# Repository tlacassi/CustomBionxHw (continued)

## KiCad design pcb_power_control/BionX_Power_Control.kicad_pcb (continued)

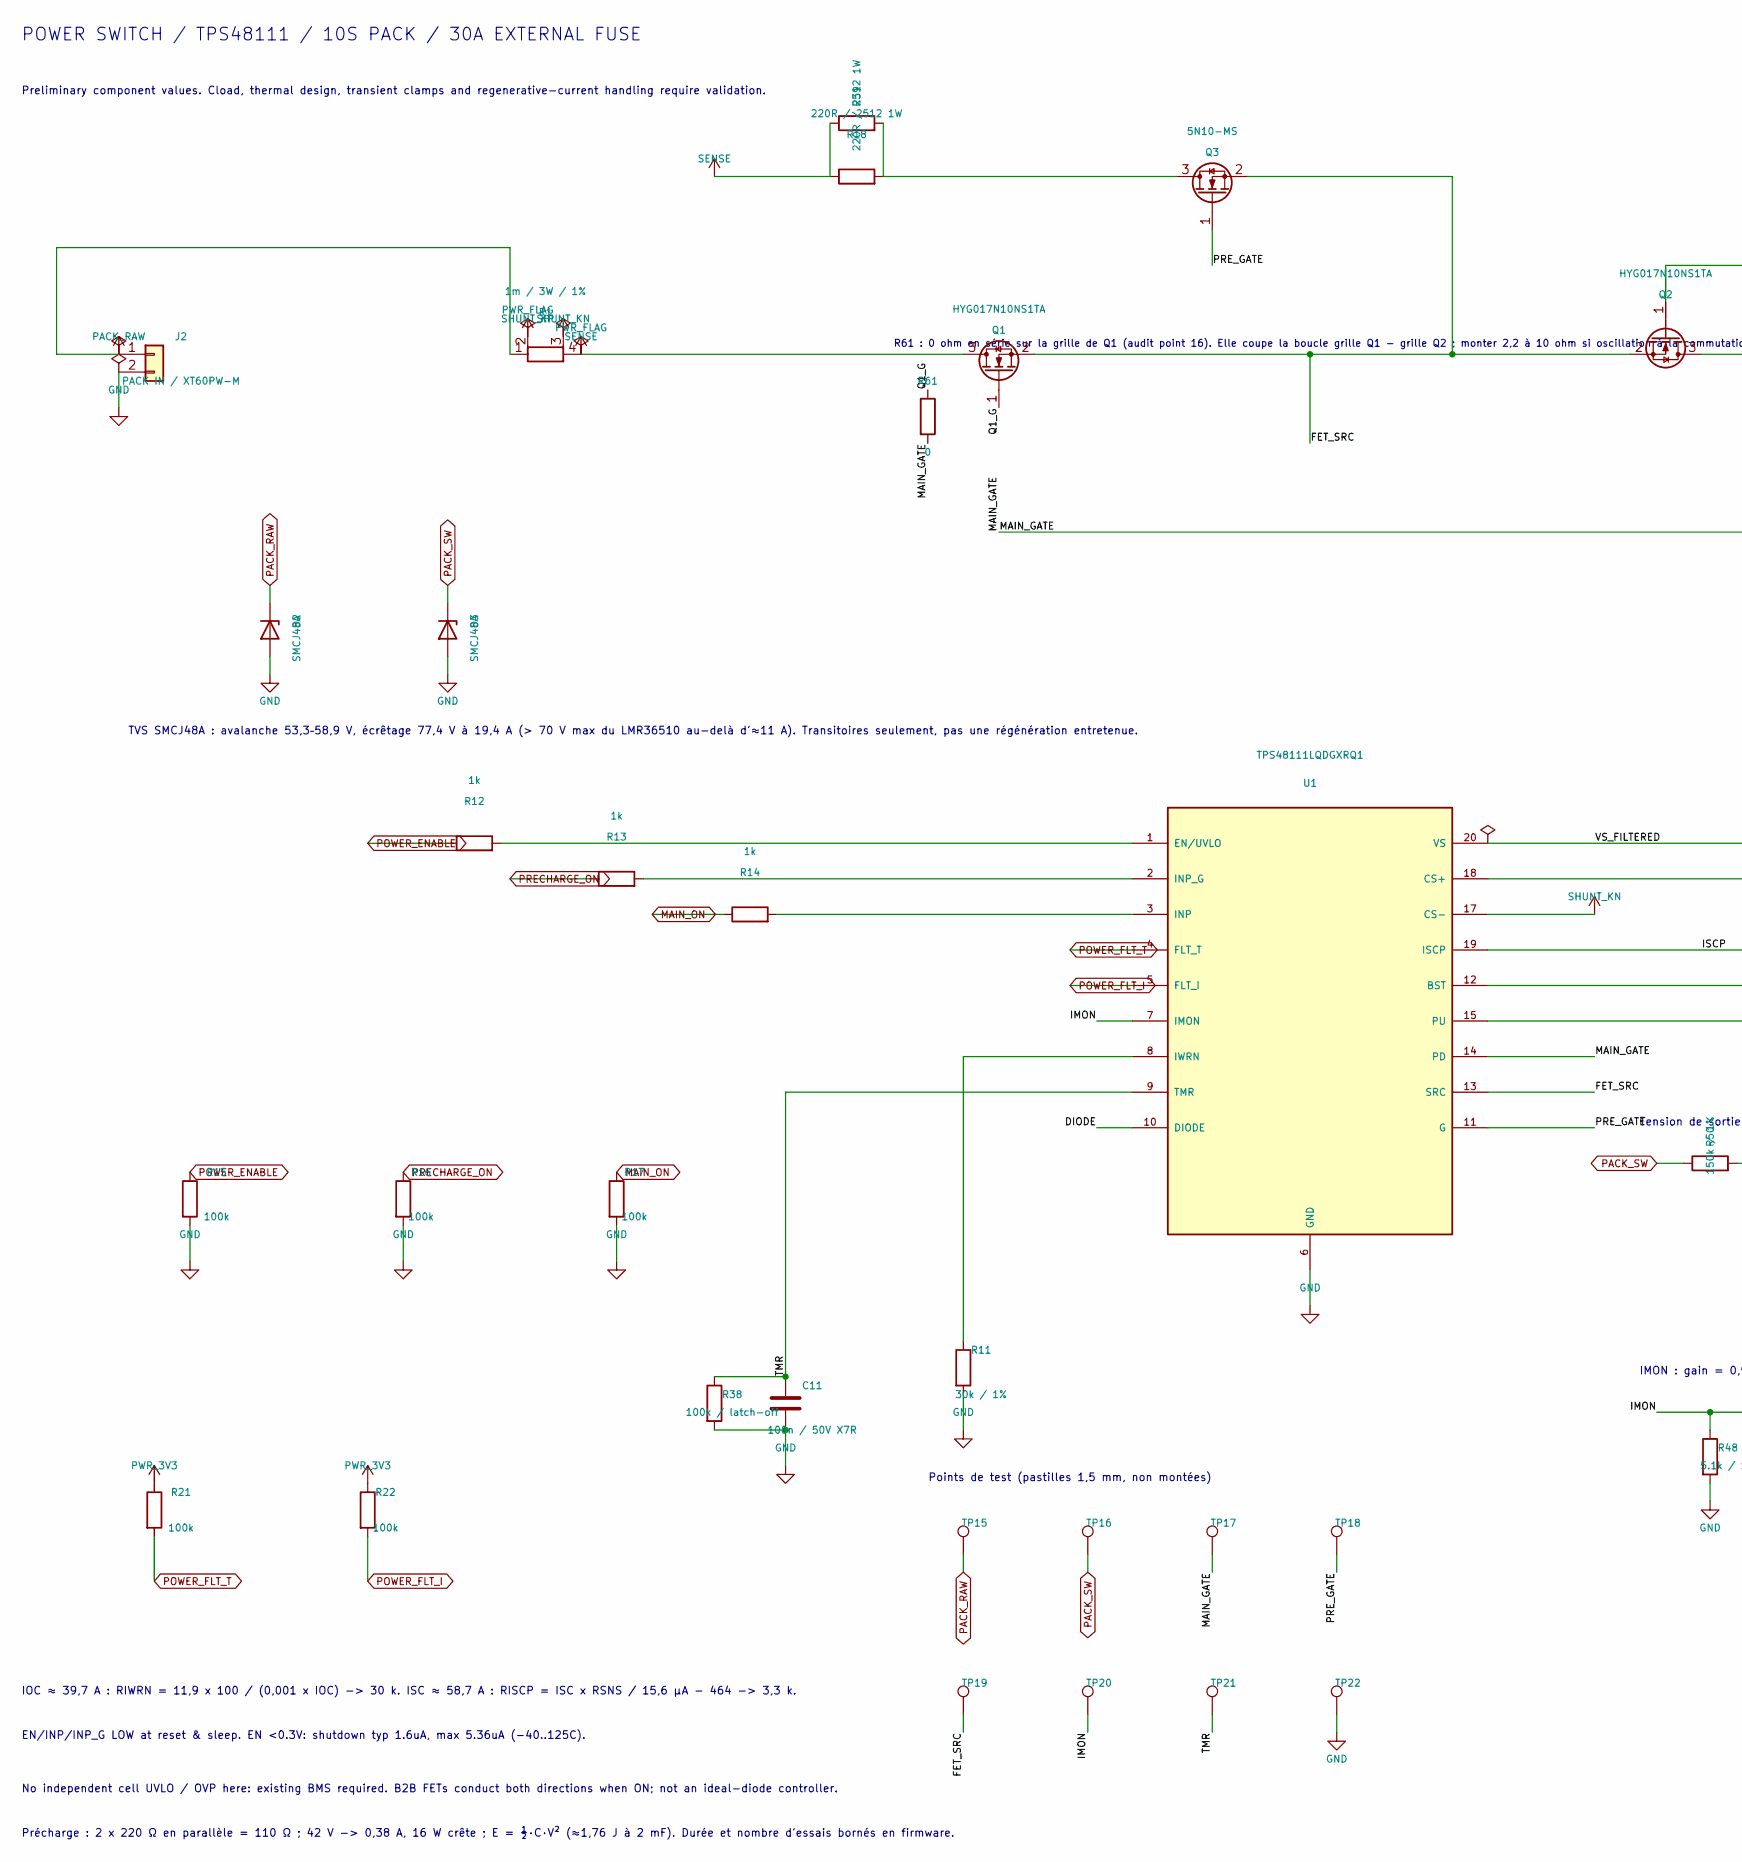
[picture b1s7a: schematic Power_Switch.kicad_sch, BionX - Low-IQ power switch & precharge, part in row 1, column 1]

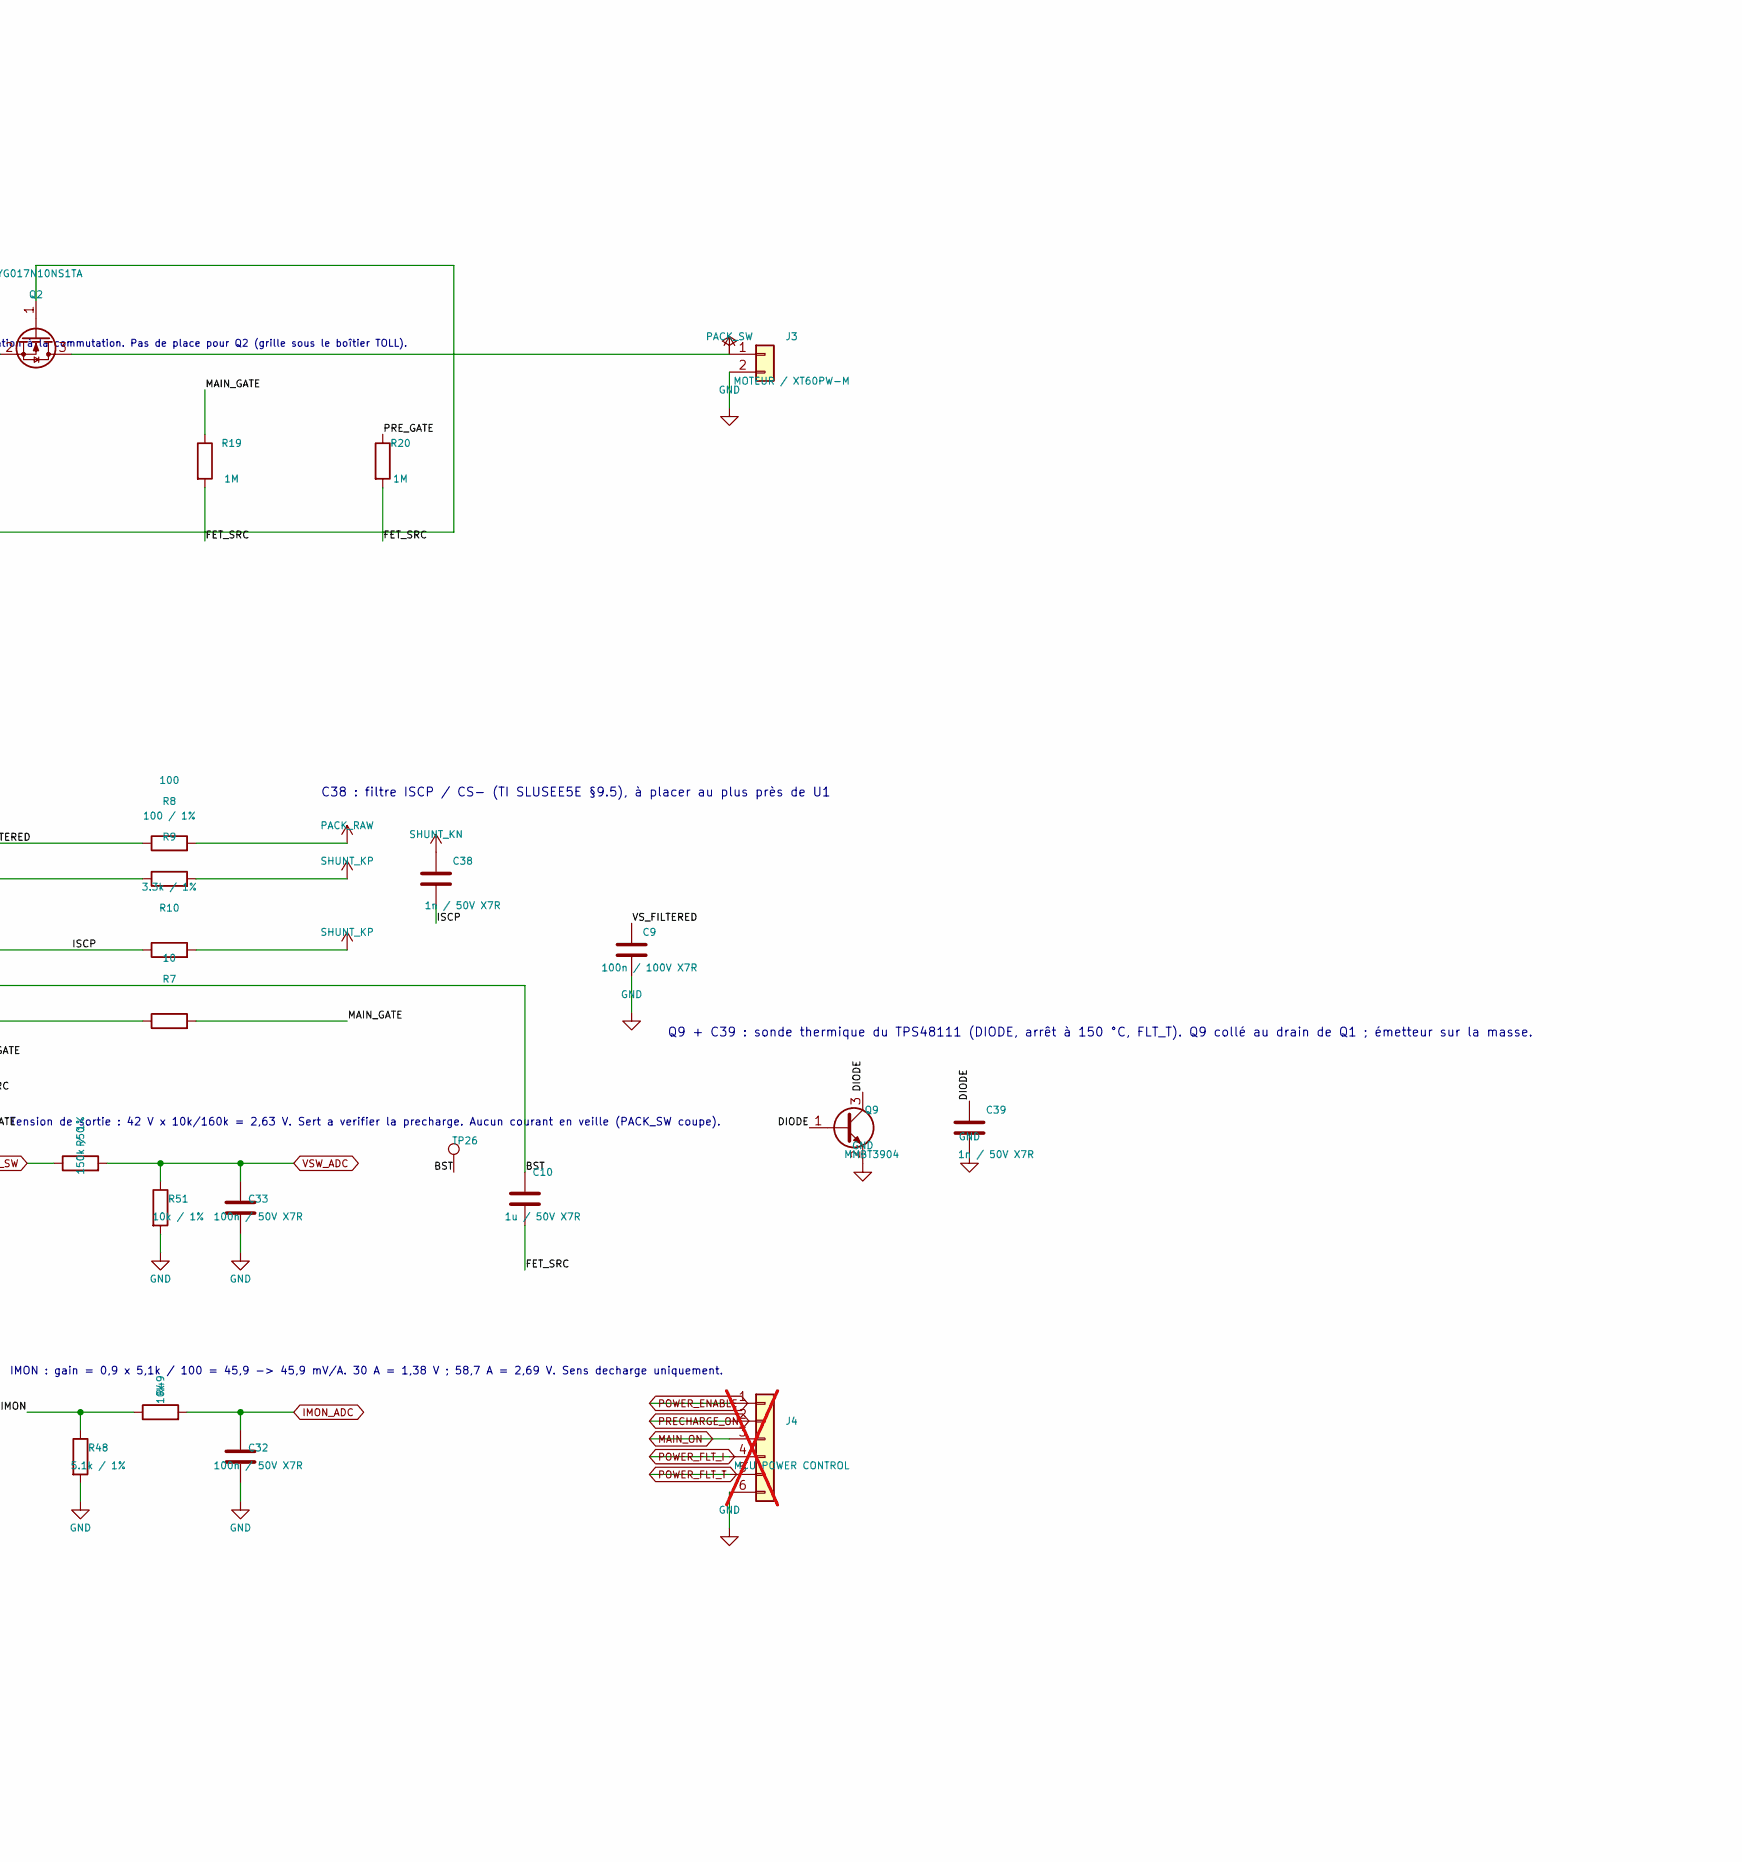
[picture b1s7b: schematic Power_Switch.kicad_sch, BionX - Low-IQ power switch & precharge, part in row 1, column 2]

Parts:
C9: 100n / 100V X7R; C_0805_2012Metric; MPN CL21B104KCC5PNC; LCSC C472809
C10: 1u / 50V X7R; C_0805_2012Metric; MPN CL21B105KBFNNNE; LCSC C28323
C11, C32, C33: 100n / 50V X7R; C_0805_2012Metric; MPN CC0805KRX7R9BB104; LCSC C49678
C38, C39: 1n / 50V X7R; C_0402_1005Metric; MPN 0402B102K500NT; LCSC C1523
D2, D3: SMCJ48A; D_SMC; MPN SMCJ48A; LCSC C19077611
J2: PACK IN / XT60PW-M; AMASS_XT60PW-M_1x02_P7.20mm_Horizontal; MPN XT60PW-M
J3: MOTEUR / XT60PW-M; AMASS_XT60PW-M_1x02_P7.20mm_Horizontal; MPN XT60PW-M
J4: MCU POWER CONTROL; PinHeader_1x06_P2.54mm_Vertical; not fitted
Q1, Q2: HYG017N10NS1TA; Infineon_PG-HSOF-8-1; MPN HYG017N10NS1TA; LCSC C5205219
Q3: 5N10-MS; SOT-23; MPN 5N10-MS; LCSC C5140036
Q9: MMBT3904; SOT-23; MPN MMBT3904; LCSC C20526
R1: 1m / 3W / 1%; R_Shunt_2512_Kelvin_RLP25; MPN RLP25FEGR001; LCSC C459678
R7: 10; R_0603_1608Metric; MPN 0603WAF100JT5E; LCSC C22859
R8: 100; R_0603_1608Metric; MPN 0603WAF1000T5E; LCSC C22775
R9: 100 / 1%; R_0603_1608Metric; MPN 0603WAF1000T5E; LCSC C22775
R10: 3.3k / 1%; R_0603_1608Metric; MPN 0603WAF3301T5E; LCSC C22978
R11: 30k / 1%; R_0603_1608Metric; MPN 0603WAF3002T5E; LCSC C22984
R12, R13, R14: 1k; R_0603_1608Metric; MPN 0603WAF1001T5E; LCSC C21190
R15, R16, R17, R21, R22: 100k; R_0603_1608Metric; MPN 0603WAF1003T5E; LCSC C25803
R18, R39: 220R / 2512 1W; R_2512_6332Metric; MPN RC2512JK-07220RL; LCSC C137008
R19, R20: 1M; R_0603_1608Metric; MPN 0603WAF1004T5E; LCSC C22935
R38: 100k / latch-off; R_0603_1608Metric; MPN 0603WAF1003T5E; LCSC C25803
R48: 5.1k / 1%; R_0603_1608Metric; MPN 0603WAF5101T5E; LCSC C23186
R49: 10k; R_0603_1608Metric; MPN 0603WAF1002T5E; LCSC C25804
R50: 150k / 1%; R_0603_1608Metric; MPN 0603WAF1503T5E; LCSC C22807
R51: 10k / 1%; R_0603_1608Metric; MPN 0603WAF1002T5E; LCSC C25804
R61: 0; R_0402_1005Metric; MPN 0402WGF0000TCE; LCSC C17168
TP15: PACK_RAW; TestPoint_Pad_D1.5mm
TP16: PACK_SW; TestPoint_Pad_D1.5mm
TP17: MAIN_GATE; TestPoint_Pad_D1.5mm
TP18: PRE_GATE; TestPoint_Pad_D1.5mm
TP19: FET_SRC; TestPoint_Pad_D1.5mm
TP20: IMON; TestPoint_Pad_D1.5mm
TP21: TMR; TestPoint_Pad_D1.5mm
TP22: GND; TestPoint_Pad_D1.5mm
TP26: BST; TestPoint_Pad_D1.0mm
U1: TPS48111LQDGXRQ1; VSSOP-19_DGX_3x5.1mm_P0.5mm; MPN TPS48111LQDGXRQ1; LCSC C17558994

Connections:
/01 Commutation et précharge/BST: C10.1, TP26.1, U1.12 (BST)
/01 Commutation et précharge/DIODE: C39.1, Q9.1 (B), Q9.3 (C), U1.10 (DIODE)
/01 Commutation et précharge/FET_SRC: C10.2, Q1.2 (S), Q2.2 (S), Q3.2 (S), R19.2, R20.2, TP19.1, U1.13 (SRC)
/01 Commutation et précharge/IMON: R48.1, R49.1, TP20.1, U1.7 (IMON)
/01 Commutation et précharge/ISCP: C38.2, R10.1, U1.19 (ISCP)
/01 Commutation et précharge/MAIN_GATE: Q2.1 (G), R7.2, R19.1, R61.2, TP17.1, U1.14 (PD)
/01 Commutation et précharge/PRE_GATE: Q3.1 (G), R20.1, TP18.1, U1.11 (G)
/01 Commutation et précharge/Q1_G: Q1.1 (G), R61.1
/01 Commutation et précharge/TMR: C11.1, R38.1, TP21.1, U1.9 (TMR)
IMON_ADC: C32.1, R49.2; also elsewhere on the board
MAIN_ON: J4.3, R14.1, R17.1; also elsewhere on the board
unnamed: Q3.3 (D), R18.2, R39.2
unnamed: R9.1, U1.18 (CS+)
unnamed: R12.2, U1.1 (EN/UVLO)
unnamed: R14.2, U1.3 (INP)
unnamed: R13.2, U1.2 (INP_G)
unnamed: R11.1, U1.8 (IWRN)
unnamed: R7.1, U1.15 (PU)
POWER_ENABLE: J4.1, R12.1, R15.1; also elsewhere on the board
POWER_FLT_I: J4.4, R22.2, U1.5 (FLT_I); also elsewhere on the board
POWER_FLT_T: J4.5, R21.2, U1.4 (FLT_T); also elsewhere on the board
PRECHARGE_ON: J4.2, R13.1, R16.1; also elsewhere on the board
PWR_3V3: R21.1, R22.1; also elsewhere on the board
SENSE: Q1.3 (D), R1.4, R18.1, R39.1
SHUNT_KP: R1.2, R9.2, R10.2
VSW_ADC: C33.1, R50.2, R51.1; also elsewhere on the board

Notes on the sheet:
EN/INP/INP_G LOW at reset & sleep. EN <0.3V: shutdown typ 1.6uA, max 5.36uA (-40..125C).
IOC ≈ 39,7 A : RIWRN = 11,9 x 100 / (0,001 x IOC) -> 30 k. ISC ≈ 58,7 A : RISCP = ISC x RSNS / 15,6 µA - 464 -> 3,3 k.
No independent cell UVLO / OVP here: existing BMS required. B2B FETs conduct both directions when ON; not an ideal-diode controller.
Précharge : 2 x 220 Ω en parallèle = 110 Ω ; 42 V -> 0,38 A, 16 W crête ; E = ½·C·V² (≈1,76 J à 2 mF). Durée et nombre d'essais bornés en firmware.
Preliminary component values. Cload, thermal design, transient clamps and regenerative-current handling require validation.
POWER SWITCH / TPS48111 / 10S PACK / 30A EXTERNAL FUSE
TVS SMCJ48A : avalanche 53,3–58,9 V, écrêtage 77,4 V à 19,4 A (> 70 V max du LMR36510 au-delà d'≈11 A). Transitoires seulement, pas une régénération entretenue.
IMON : gain = 0,9 x 5,1k / 100 = 45,9 -> 45,9 mV/A. 30 A = 1,38 V ; 58,7 A = 2,69 V. Sens decharge uniquement.
Tension de sortie : 42 V x 10k/160k = 2,63 V. Sert a verifier la precharge. Aucun courant en veille (PACK_SW coupe).
Points de test (pastilles 1,5 mm, non montées)
C38 : filtre ISCP / CS- (TI SLUSEE5E §9.5), à placer au plus près de U1
Q9 + C39 : sonde thermique du TPS48111 (DIODE, arrêt à 150 °C, FLT_T). Q9 collé au drain de Q1 ; émetteur sur la masse.
R61 : 0 ohm en série sur la grille de Q1 (audit point 16). Elle coupe la boucle grille Q1 - grille Q2 ; monter 2,2 à 10 ohm si oscillation à la commutation. Pas de place pour Q2 (grille sous le boîtier TOLL).

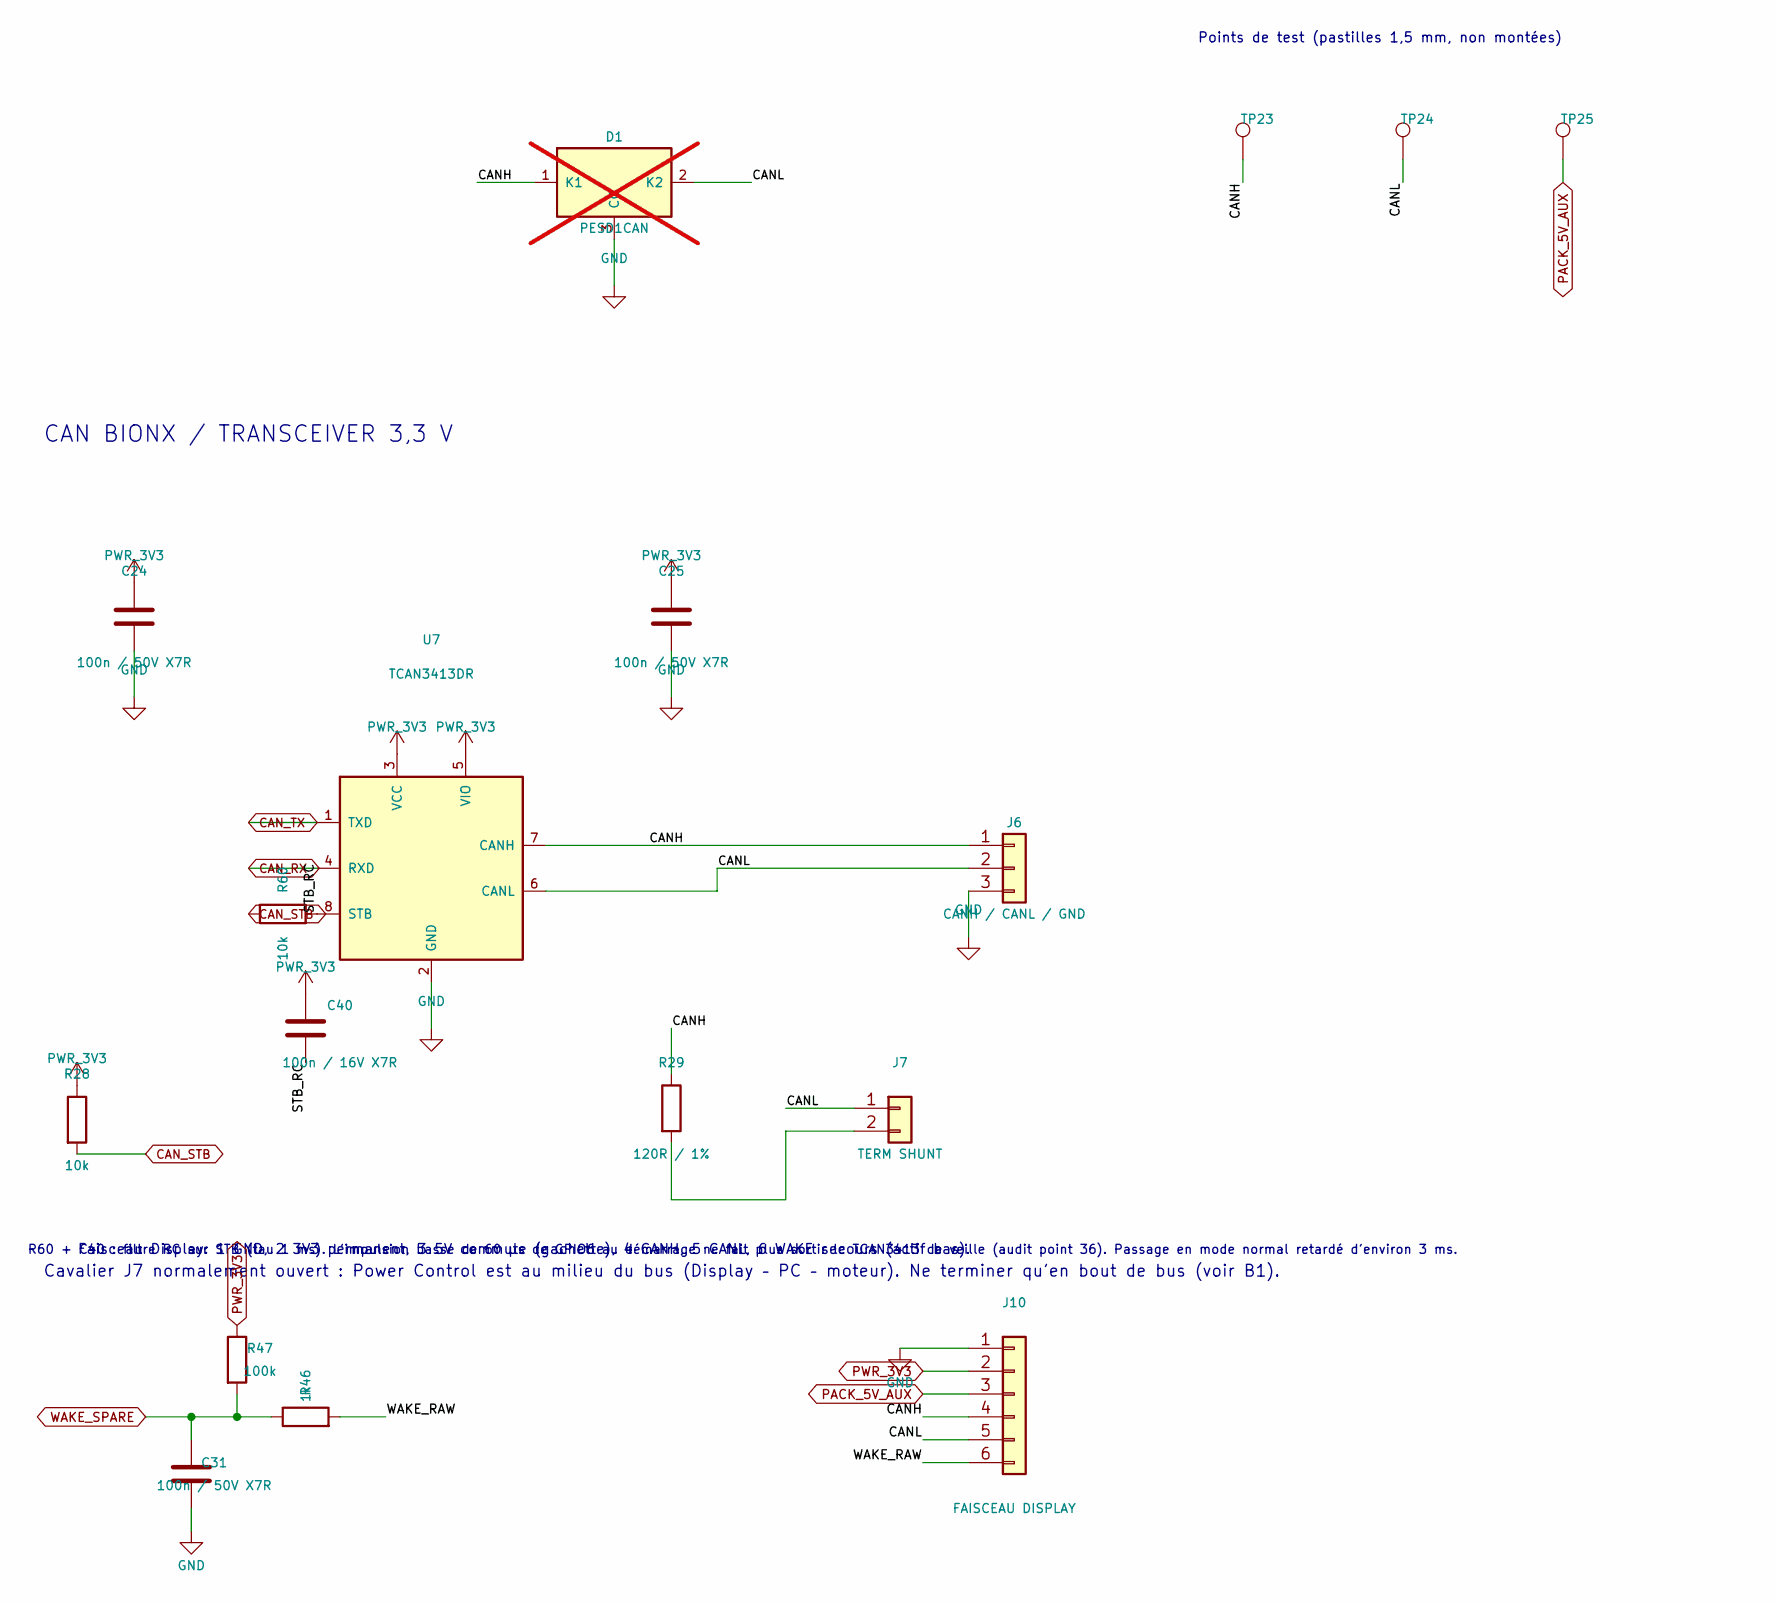
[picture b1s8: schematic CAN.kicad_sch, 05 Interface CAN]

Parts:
C24, C25, C31: 100n / 50V X7R; C_0805_2012Metric; MPN CC0805KRX7R9BB104; LCSC C49678
C40: 100n / 16V X7R; C_0402_1005Metric; MPN CL05B104KO5NNNC; LCSC C1525
D1: PESD1CAN; SOT-23; MPN PESD1CAN; LCSC C343993; not fitted
J6: CANH / CANL / GND; JST_XH_B3B-XH-A_1x03_P2.50mm_Vertical; MPN B3B-XH-A
J7: TERM SHUNT; PinHeader_1x02_P2.54mm_Vertical
J10: FAISCEAU DISPLAY; JST_XH_B6B-XH-A_1x06_P2.50mm_Vertical; MPN B6B-XH-A
R28: 10k; R_0603_1608Metric; MPN 0603WAF1002T5E; LCSC C25804
R29: 120R / 1%; R_0603_1608Metric; MPN 0603WAF1200T5E; LCSC C22787
R46: 1k; R_0603_1608Metric; MPN 0603WAF1001T5E; LCSC C21190
R47: 100k; R_0603_1608Metric; MPN 0603WAF1003T5E; LCSC C25803
R60: 10k; R_0402_1005Metric; MPN 0402WGF1002TCE; LCSC C25744
TP23: CANH; TestPoint_Pad_D1.5mm
TP24: CANL; TestPoint_Pad_D1.5mm
TP25: PACK_5V_AUX; TestPoint_Pad_D1.5mm
U7: TCAN3413DR; SOIC-8_3.9x4.9mm_P1.27mm; MPN TCAN3413DR; LCSC C22433320

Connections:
/05 Interface CAN/CANH: D1.1 (K1), J6.1, J10.4, R29.1, TP23.1, U7.7 (CANH)
/05 Interface CAN/CANL: D1.2 (K2), J6.2, J7.1, J10.5, TP24.1, U7.6 (CANL)
/05 Interface CAN/STB_RC: C40.2, R60.2, U7.8 (STB)
/05 Interface CAN/WAKE_RAW: J10.6, R46.2
CAN_RX: U7.4 (RXD); also elsewhere on the board
CAN_STB: R28.2, R60.1; also elsewhere on the board
CAN_TX: U7.1 (TXD); also elsewhere on the board
unnamed: J7.2, R29.2
PACK_5V_AUX: J10.3, TP25.1; also elsewhere on the board
PWR_3V3: C24.1, C25.1, C40.1, J10.2, R28.1, R47.1, U7.3 (VCC), U7.5 (VIO); also elsewhere on the board
WAKE_SPARE: C31.1, R46.1, R47.2; also elsewhere on the board

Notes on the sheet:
CAN BIONX / TRANSCEIVER 3,3 V
Cavalier J7 normalement ouvert : Power Control est au milieu du bus (Display – PC – moteur). Ne terminer qu'en bout de bus (voir B1).
Faisceau Display: 1 GND, 2 3V3 permanent, 3 5V commute (gachette), 4 CANH, 5 CANL, 6 WAKE secours (actif bas).
Points de test (pastilles 1,5 mm, non montées)
R60 + C40 : filtre RC sur STB (tau 1 ms). L'impulsion basse de 60 µs de GPIO6 au démarrage ne fait plus sortir le TCAN3413 de veille (audit point 36). Passage en mode normal retardé d'environ 3 ms.

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
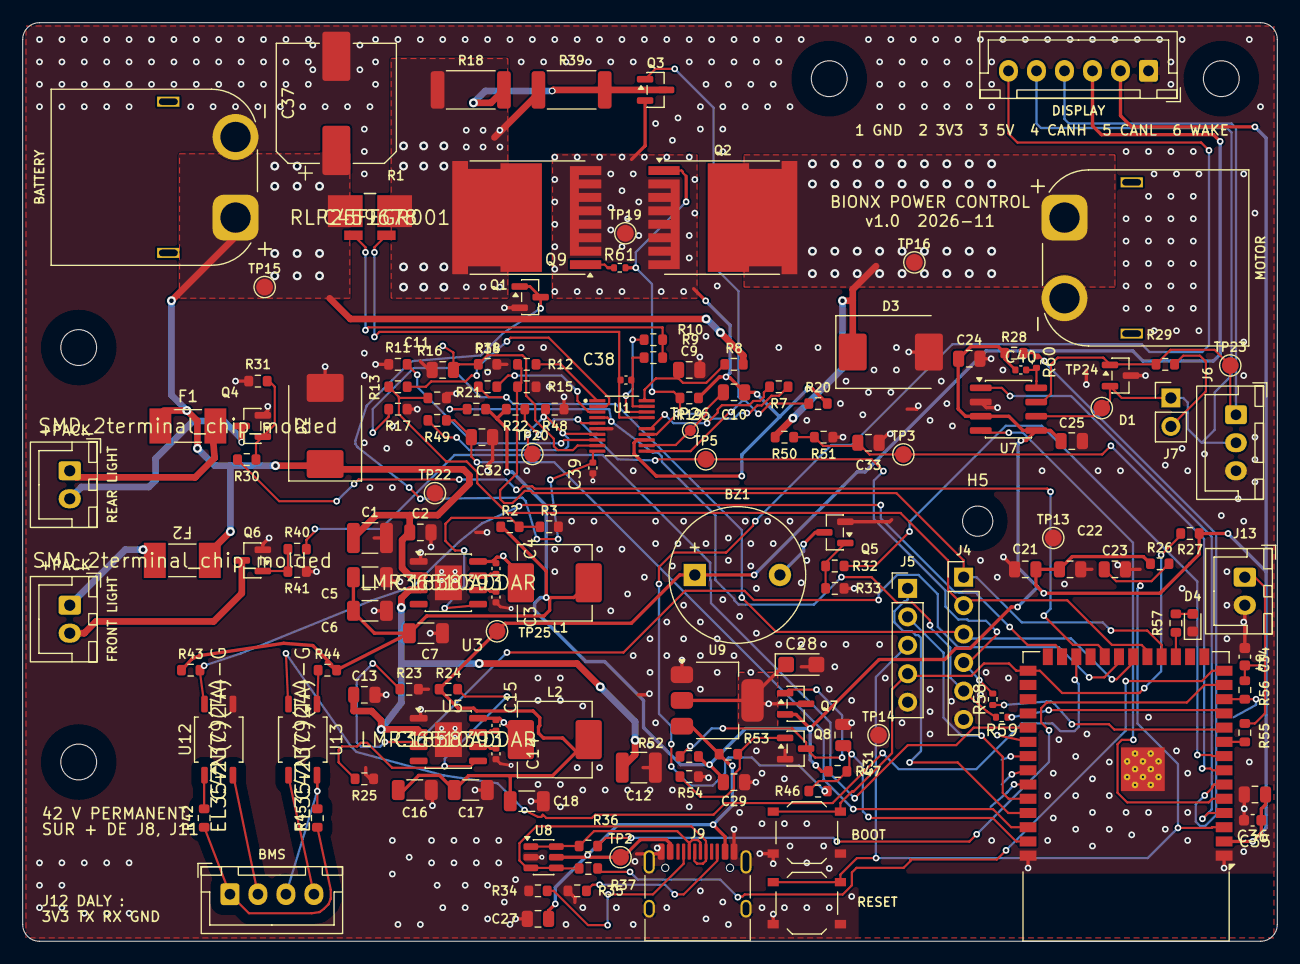
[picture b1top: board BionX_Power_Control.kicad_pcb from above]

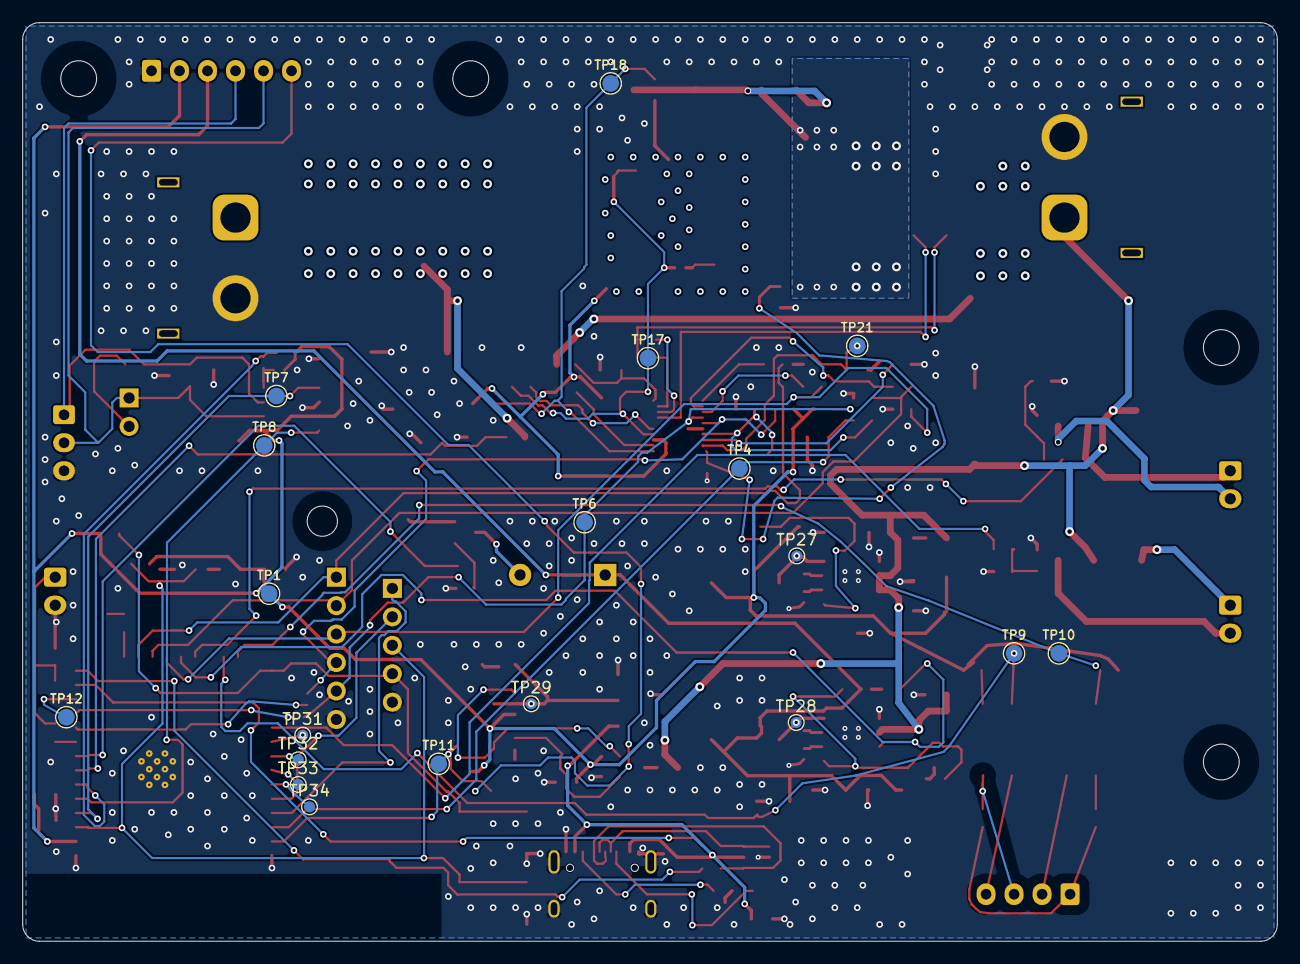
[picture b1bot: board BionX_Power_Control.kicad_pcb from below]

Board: 4 copper layers, 112.0 x 82.0 mm, 172 parts (19 on the bottom side), 94 nets.

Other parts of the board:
H1, H2, H3, H4: M3; MountingHole_3.2mm_M3
H5: MountingHole_M2.5; MountingHole_2.7mm_M2.5

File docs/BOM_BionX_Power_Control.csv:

"Reference","Value","Footprint","MPN","LCSC","Qty","DNP","Montage"
"BZ1","TMB12A05 / 5V actif","Buzzer_Beeper:Buzzer_12x9.5RM7.6","TMB12A05","","1","","manuel"
"C1,C12","2.2u / 100V X7R","Capacitor_SMD:C_1210_3225Metric","CL32B225KCJSNNE","C55151","2","",""
"C2,C9,C13","100n / 100V X7R","Capacitor_SMD:C_0805_2012Metric","CL21B104KCC5PNC","C472809","3","",""
"C3,C14","1u / 25V X5R","Capacitor_SMD:C_0402_1005Metric","CL05A105KA5NQNC","C52923","2","",""
"C4,C15","100n / 50V X7R","Capacitor_SMD:C_0402_1005Metric","CL05B104KB54PNC","C307331","2","",""
"C5,C6,C7,C16,C17,C18","22u / 25V X5R","Capacitor_SMD:C_1206_3216Metric","CL31A226KAHNNNE","C12891","6","",""
"C10,C23,C27,C29","1u / 50V X7R","Capacitor_SMD:C_0805_2012Metric","CL21B105KBFNNNE","C28323","4","",""
"C11,C21,C24,C25,C31,C32,C33","100n / 50V X7R","Capacitor_SMD:C_0805_2012Metric","CC0805KRX7R9BB104","C49678","7","",""
"C22,C35","10u / 25V X5R","Capacitor_SMD:C_0805_2012Metric","CL21A106KAYNNNE","C15850","2","",""
"C28","10u / 16V tantale","Capacitor_Tantalum_SMD:CP_EIA-3216-18_Kemet-A","TAJA106K016RNJ","C7171","1","",""
"C34,C36","100n / 50V X7R","Capacitor_SMD:C_0603_1608Metric","CC0603KRX7R9BB104","C14663","2","",""
"C37","100u / 63V alu","Capacitor_SMD:CP_Elec_10x10.5","CS1J101M-CRG10","C116430","1","",""
"C38,C39","1n / 50V X7R","Capacitor_SMD:C_0402_1005Metric","0402B102K500NT","C1523","2","",""
"C40","100n / 16V X7R","Capacitor_SMD:C_0402_1005Metric","CL05B104KO5NNNC","C1525","1","",""
"D2,D3","SMCJ48A","Diode_SMD:D_SMC","SMCJ48A","C19077611","2","",""
"D4","KT-0603R rouge","LED_SMD:LED_0603_1608Metric","KT-0603R","C2286","1","",""
"F1,F2","Fusible 1A 125V rapide","Fuse:Fuse_Littelfuse-NANO2-451_453","0451001.MRL","C3099","2","",""
"J2","PACK IN / XT60PW-M","Connector_AMASS:AMASS_XT60PW-M_1x02_P7.20mm_Horizontal","XT60PW-M","","1","","manuel"
"J3","MOTEUR / XT60PW-M","Connector_AMASS:AMASS_XT60PW-M_1x02_P7.20mm_Horizontal","XT60PW-M","","1","","manuel"
"J4","MCU POWER CONTROL","Connector_PinHeader_2.54mm:PinHeader_1x06_P2.54mm_Vertical","","","1","DNP","manuel"
"J5","UART0 / 3.3V LOGIC","Connector_PinHeader_2.54mm:PinHeader_1x05_P2.54mm_Vertical","","","1","DNP","manuel"
"J6","CANH / CANL / GND","Connector_JST:JST_XH_B3B-XH-A_1x03_P2.50mm_Vertical","B3B-XH-A","","1","","manuel"
"J7","TERM SHUNT","Connector_PinHeader_2.54mm:PinHeader_1x02_P2.54mm_Vertical","","","1","","manuel"
"J8","FEU ARRIERE / tension pack","Connector_JST:JST_XH_B2B-XH-A_1x02_P2.50mm_Vertical","B2B-XH-A","","1","","manuel"
"J9","USB-C USB 2.0","Connector_USB:USB_C_Receptacle_HRO_TYPE-C-31-M-12","TYPE-C-31-M-12","C165948","1","",""
"J10","FAISCEAU DISPLAY","Connector_JST:JST_XH_B6B-XH-A_1x06_P2.50mm_Vertical","B6B-XH-A","","1","","manuel"
"J11","FEU AVANT / tension pack","Connector_JST:JST_XH_B2B-XH-A_1x02_P2.50mm_Vertical","B2B-XH-A","","1","","manuel"
"J12","DALY UART: 3V3 TX RX GND","Connector_JST:JST_XH_B4B-XH-A_1x04_P2.50mm_Vertical","B4B-XH-A","","1","","manuel"
"J13","SONDE TEMP / CTN 10k","Connector_JST:JST_XH_B2B-XH-A_1x02_P2.50mm_Vertical","B2B-XH-A","","1","","manuel"
"L1,L2","22uH / 3A","Inductor_SMD:L_Changjiang_FXL0630","SRG0630-220-M","C53462993","2","",""
"Q1,Q2","HYG017N10NS1TA","Package_TO_SOT_SMD:Infineon_PG-HSOF-8-1","HYG017N10NS1TA","C5205219","2","",""
"Q3,Q4,Q6","5N10-MS","Package_TO_SOT_SMD:SOT-23","5N10-MS","C5140036","3","",""
"Q5,Q8","AO3400A","Package_TO_SOT_SMD:SOT-23","AO3400A","C20917","2","",""
"Q7","AO3401A","Package_TO_SOT_SMD:SOT-23","AO3401A","C15127","1","",""
"Q9","MMBT3904","Package_TO_SOT_SMD:SOT-23","MMBT3904","C20526","1","",""
"R1","1m / 3W / 1%","BionX:R_Shunt_2512_Kelvin_RLP25","RLP25FEGR001","C459678","1","",""
"R2","47k / 1%","Resistor_SMD:R_0603_1608Metric","0603WAF4702T5E","C25819","1","",""
"R3,R25","20k / 1%","Resistor_SMD:R_0603_1608Metric","0603WAF2002T5E","C4184","2","",""
"R7","10","Resistor_SMD:R_0603_1608Metric","0603WAF100JT5E","C22859","1","",""
"R8","100","Resistor_SMD:R_0603_1608Metric","0603WAF1000T5E","C22775","1","",""
"R9","100 / 1%","Resistor_SMD:R_0603_1608Metric","0603WAF1000T5E","C22775","1","",""
"R10","3.3k / 1%","Resistor_SMD:R_0603_1608Metric","0603WAF3301T5E","C22978","1","",""
"R11","30k / 1%","Resistor_SMD:R_0603_1608Metric","0603WAF3002T5E","C22984","1","",""
"R12,R13,R14,R46,R56,R57","1k","Resistor_SMD:R_0603_1608Metric","0603WAF1001T5E","C21190","6","",""
"R15,R16,R17,R21,R22,R23,R31,R33,R41,R47,R52,R53,R54","100k","Resistor_SMD:R_0603_1608Metric","0603WAF1003T5E","C25803","13","",""
"R18,R39","220R / 2512 1W","Resistor_SMD:R_2512_6332Metric","RC2512JK-07220RL","C137008","2","",""
"R19,R20","1M","Resistor_SMD:R_0603_1608Metric","0603WAF1004T5E","C22935","2","",""
"R24","82k / 1%","Resistor_SMD:R_0603_1608Metric","0603WAF8202T5E","C23254","1","",""
"R26,R27,R28,R49","10k","Resistor_SMD:R_0603_1608Metric","0603WAF1002T5E","C25804","4","",""
"R29","120R / 1%","Resistor_SMD:R_0603_1608Metric","0603WAF1200T5E","C22787","1","",""
"R30,R32,R40","100R","Resistor_SMD:R_0603_1608Metric","0603WAF1000T5E","C22775","3","",""
"R34,R35,R48","5.1k / 1%","Resistor_SMD:R_0603_1608Metric","0603WAF5101T5E","C23186","3","",""
"R36,R37","22R","Resistor_SMD:R_0603_1608Metric","0603WAF220JT5E","C23345","2","",""
"R38","100k / latch-off","Resistor_SMD:R_0603_1608Metric","0603WAF1003T5E","C25803","1","",""
"R42,R44","470R","Resistor_SMD:R_0603_1608Metric","0603WAF4700T5E","C23179","2","",""
"R43,R45","2.2k","Resistor_SMD:R_0603_1608Metric","0603WAF2201T5E","C4190","2","",""
"R50","150k / 1%","Resistor_SMD:R_0603_1608Metric","0603WAF1503T5E","C22807","1","",""
"R51,R55","10k / 1%","Resistor_SMD:R_0603_1608Metric","0603WAF1002T5E","C25804","2","",""
"R58,R59","1k","Resistor_SMD:R_0402_1005Metric","0402WGF1001TCE","C11702","2","",""
"R60","10k","Resistor_SMD:R_0402_1005Metric","0402WGF1002TCE","C25744","1","",""
"R61","0","Resistor_SMD:R_0402_1005Metric","0402WGF0000TCE","C17168","1","",""
"SW1","BOOT","Button_Switch_SMD:SW_Push_1P1T_XKB_TS-1187A","TS-1187A-B-A-B","C318884","1","",""
"SW2","RESET","Button_Switch_SMD:SW_Push_1P1T_XKB_TS-1187A","TS-1187A-B-A-B","C318884","1","",""
"U1","TPS48111LQDGXRQ1","BionX:VSSOP-19_DGX_3x5.1mm_P0.5mm","TPS48111LQDGXRQ1","C17558994","1","",""
"U3,U5","LMR36510ADDAR","Package_SO:HSOP-8-1EP_3.9x4.9mm_P1.27mm_EP2.41x3.1mm","LMR36510ADDAR","C1858393","2","",""
"U4","ESP32-S3-WROOM-1-N8","RF_Module:ESP32-S3-WROOM-1","ESP32-S3-WROOM-1-N8","C2913198","1","",""
"U7","TCAN3413DR","Package_SO:SOIC-8_3.9x4.9mm_P1.27mm","TCAN3413DR","C22433320","1","",""
"U8","USBLC6-2SC6","Package_TO_SOT_SMD:SOT-23-6","USBLC6-2SC6","C7519","1","",""
"U9","AMS1117-3.3","Package_TO_SOT_SMD:SOT-223-3_TabPin2","AMS1117-3.3","C6186","1","",""
"U12,U13","EL357N(C)(TA)-G","BionX:SOP-4_EL357N_Everlight","EL357N(C)(TA)-G","C42379244","2","",""
